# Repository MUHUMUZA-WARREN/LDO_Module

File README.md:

This is a simple 3.3V LDO (Low Drop Out) module PCB.

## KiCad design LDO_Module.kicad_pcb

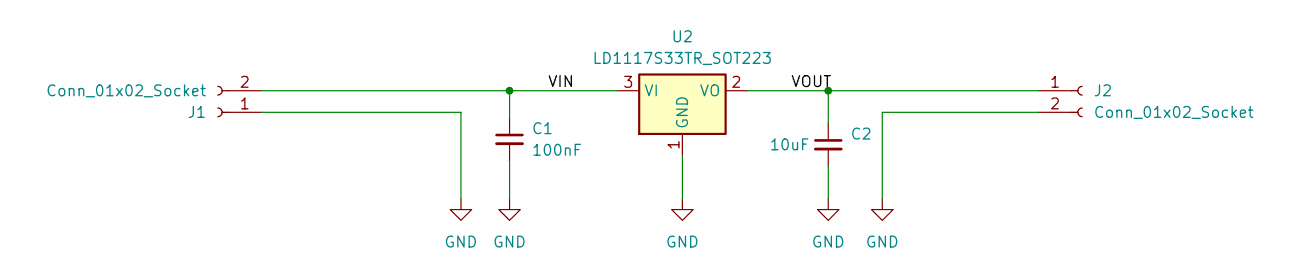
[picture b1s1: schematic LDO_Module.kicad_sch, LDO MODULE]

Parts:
C1: 100nF; C_1812_4532Metric; MFR. Part # 1812B104K631NT
C2: 10uF; C_1812_4532Metric; MFR. Part # FS43X106K500EGG
J1, J2: Conn_01x02_Socket; JST_EH_S2B-EH_1x02_P2.50mm_Horizontal; MFR. Part # S2B-EH(LF)(SN)
U2: LD1117S33TR_SOT223; SOT-223-3_TabPin2; MFR. Part # LD1117S33CTR

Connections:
/VIN: C1.1, J1.2, U2.3 (VI)
/VOUT: C2.1, J2.1, U2.2 (VO)
GND: C1.2, C2.2, J1.1, J2.2, U2.1 (GND)

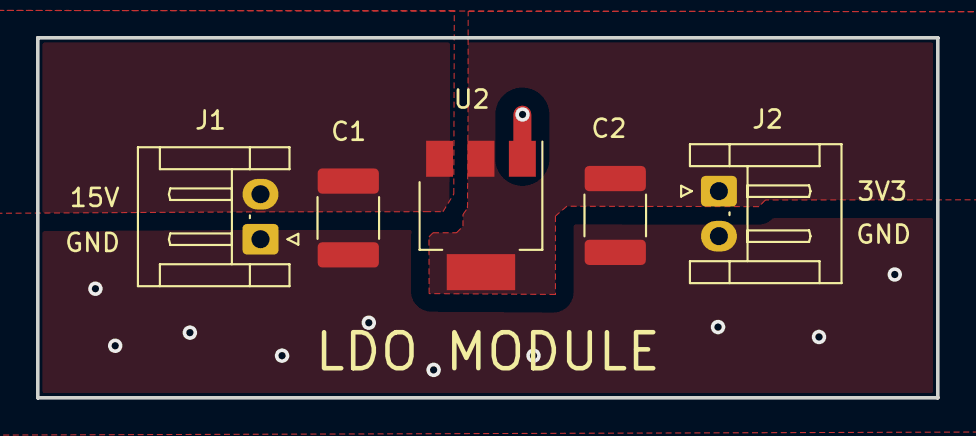
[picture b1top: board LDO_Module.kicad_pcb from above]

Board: 2 copper layers, 50.0 x 20.0 mm, 5 parts (0 on the bottom side), 3 nets.

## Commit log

2024-09-22 Create README.md
    Added a readme file.
2024-09-22 Update README.md
    Added a picture of the board
2024-10-29 Added a 3D view png and removed back up folder.
